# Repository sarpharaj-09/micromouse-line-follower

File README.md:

# Micromouse Line Follower

 **Project Status: In Development** 

A line-following micromouse robot project combining hardware design (KiCAD PCB layouts) with firmware development. This repository includes both Arduino Nano and ESP32 implementations, with comprehensive testing code and calibration tools.

## Overview

This project aims to build a reliable line-following robot using:
- **QTR-8 sensor array** for line detection
- **TB6612FNG motor driver** for motor control
- **Maze solving algorithm** with path simplification
- **PID control** for stable line following
- Dual MCU support: **ESP32** (primary) and **Arduino Nano** (testing)

The firmware includes motor control, PID tuning, sensor calibration, and a maze-solving algorithm that records and simplifies paths.

## Hardware

### Microcontrollers
- **ESP32 Development Board** (primary target)
- **Arduino Nano** (for testing and prototyping)

### Components
- **Motor Driver**: TB6612FNG
- **Line Sensors**: QTR-8 analog/RC sensor array
- **Motors**: DC motors for wheels
- **Power**: Battery pack
- **Display**: DM-OLED096 (0.96" OLED) - in design
- **Miscellaneous**: Jumper wires, resistors, capacitors

## Project Structure

```
micromouse-line-follower/
 Arduino_Nano/               # Arduino Nano PCB design (KiCAD)
    pcb_v1/                # Version 1 PCB layout
        DM-OLED096-636/    # OLED display footprint & symbol
        ESP32-DEVKIT-V1/   # ESP32 footprint & symbol
        MP1584_buck/       # Buck converter module
        kikad_dsign.*      # KiCAD project files
 ESP32/                      # ESP32 PCB design (KiCAD)
    pcb_v1/                # Version 1 PCB layout
        DM-OLED096-636/    # OLED display footprint & symbol
        ESP32-DEVKIT-V1/   # ESP32 footprint & symbol
        lineMazeSolver.*   # KiCAD project files
 micromouse_v1/             # Main firmware project (PlatformIO)
    micromouse_v1/
        platformio.ini     # PlatformIO configuration
        include/           # Header files
        lib/               # Dependencies (QTRSensors, TB6612FNG)
        src/
           main.cpp       # Main firmware with maze solving & PID
        test/              # Unit tests
 testing_phase_code/        # Standalone test sketches
    ESP32_test_code/       # ESP32-specific tests
       qtrSensor.ino     # QTR sensor test
    Nano_test_code/        # Arduino Nano tests
        Moter_test/        # Motor driver tests
        PID_Bluethooth/    # Bluetooth PID tuning
        plotter/           # Serial plotter data
        QTR_test/          # QTR sensor calibration
 README.md
```

## Firmware Features

### Current Implementation (main.cpp)
- **8-channel QTR sensor** integration with calibration
- **PID-based line following** with configurable gains (Kp, Kd)
- **Maze solving algorithm** with wall detection and path recording
- **Path simplification** to optimize shortest route
- **Motor control** with variable speed and direction
- **Turn decision logic** (left, straight, right)

### Pin Configuration (Arduino Nano)
```
Motor Control:
  - Motor 1: AIN1=4, AIN2=5, PWMA=3
  - Motor 2: BIN1=8, BIN2=9, PWMB=6
Control:
  - Switches: SW1=10, SW2=11, SW3=12
  - LED: 7
```

## Getting Started

### Prerequisites

- [PlatformIO](https://platformio.org/) (for ESP32 development)
- [Arduino IDE](https://www.arduino.cc/en/software) (for Nano sketches)
- Required libraries:
  - `SparkFun_TB6612` (Motor Driver)
  - `QTRSensors` (Line Sensor Array)

### Building & Uploading (PlatformIO/ESP32)

```powershell
cd micromouse_v1/micromouse_v1
pio run              # Build
pio run -t upload    # Upload to connected ESP32
```

### Testing (Arduino Nano)

1. Open Arduino IDE
2. Load a test sketch: `testing_phase_code/Nano_test_code/<test_folder>/<sketch>.ino`
3. Install dependencies via Library Manager
4. Select board (Arduino Nano) and COM port
5. Upload

### Test Sketches Available

| Sketch | Purpose |
|--------|---------|
| `Moter_test` | Test TB6612 motor driver (forward, backward, turn) |
| `QTR_test` | Read raw QTR sensor values and calibrate |
| `PID_Bluethooth` | Wireless PID tuning via Bluetooth serial |
| `plotter` | Stream sensor data for Serial Plotter visualization |

## Development Workflow

- **Feature branches**: Use `wip/*` prefix for work-in-progress branches
- **Main branch**: Keep stable with tested, documented commits
- **Testing**: Validate on both hardware and in simulation before merging
- **Documentation**: Update this README and code comments when adding features

## PCB Design Status

- **Arduino Nano v1**: In design phase - includes OLED display, buck converter
- **ESP32 v1**: In design phase - primary development board layout

## Troubleshooting

### Sensor Calibration Issues
- Run `QTR_test` to verify raw sensor values
- Check sensor array alignment over the line
- Verify power supply voltage (QTR operates 3.3-5V)

### Motor Control Issues
- Use `Moter_test` to verify TB6612 pin connections
- Check PWM pins are available on your MCU
- Verify motor power supply is adequate

### PID Tuning
- Use `PID_Bluethooth` for real-time parameter adjustment
- Start with low Kp/Kd values and increase gradually
- Monitor motor oscillation and response time

## Contributing

Contributions welcome! Please:
1. Create a feature branch (`wip/feature-name`)
2. Test thoroughly on hardware
3. Submit a pull request with clear description
4. Update documentation as needed

## License

This project is licensed under the terms specified in `LICENSE`.

---

**Last Updated**: January 2026  
**Note**: This project is actively developed. Features and documentation are updated frequently.

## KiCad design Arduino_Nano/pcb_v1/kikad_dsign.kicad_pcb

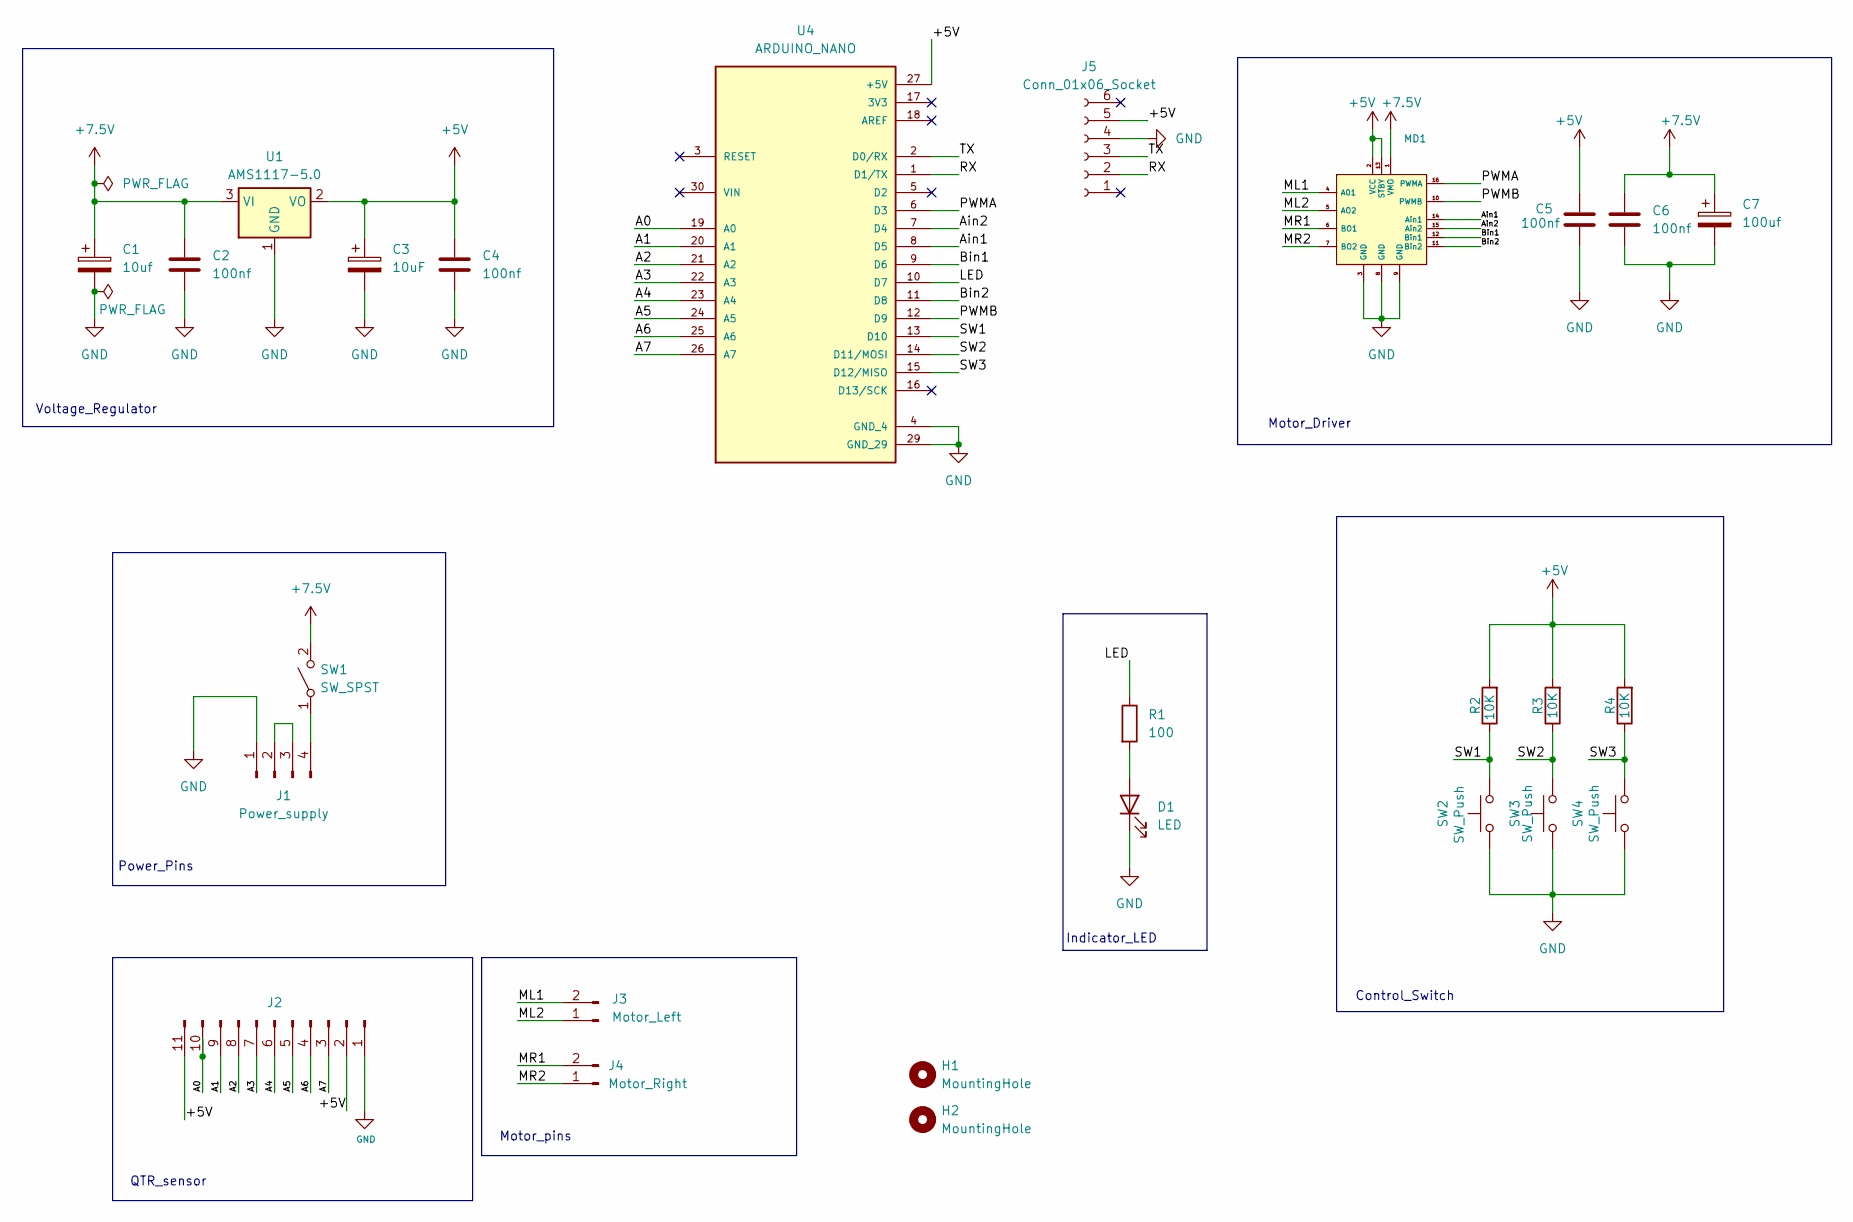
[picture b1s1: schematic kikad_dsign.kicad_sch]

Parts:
C1: 10uf; CP_Radial_D6.3mm_P2.50mm
C2, C4, C5, C6: 100nf; C_Disc_D3.8mm_W2.6mm_P2.50mm
C3: 10uF; CP_Radial_D6.3mm_P2.50mm
C7: 100uf; CP_Radial_D6.3mm_P2.50mm
D1: LED; LED_D5.0mm
H1, H2: MountingHole; MountingHole_2.5mm
J1: Power_supply; PinHeader_1x04_P2.54mm_Vertical
J2: Conn_01x11_Pin; PinHeader_1x11_P2.54mm_Vertical
J3: Motor_Left; PinHeader_1x02_P2.54mm_Vertical
J4: Motor_Right; PinHeader_1x02_P2.54mm_Vertical
J5: Conn_01x06_Socket
MD1: tbfng motor driver
R1: 100; R_Axial_DIN0207_L6.3mm_D2.5mm_P7.62mm_Horizontal
R2, R3, R4: 10K; R_Axial_DIN0207_L6.3mm_D2.5mm_P7.62mm_Horizontal
SW1: SW_SPST; PinHeader_1x02_P2.54mm_Vertical
SW2, SW3, SW4: SW_Push; SW_PUSH_6mm
U1: AMS1117-5.0; SOT-223-3_TabPin2
U4: ARDUINO_NANO; Arduino_Nano; PARTREV 30/06/2021

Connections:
+5V: C3.1, C4.1, C5.2, J2.2, J2.11, J5.5, MD1.2 (VCC), MD1.13 (STBY), R2.2, R3.2, R4.2, U1.2 (VO), U4.27 (+5V)
+7.5V: C1.1, C2.1, C6.1, C7.1, MD1.1 (VMO), SW1.2 (B), U1.3 (VI)
/A0: J2.10, U4.19 (A0)
/A1: J2.9, U4.20 (A1)
/A2: J2.8, U4.21 (A2)
/A3: J2.7, U4.22 (A3)
/A4: J2.6, U4.23 (A4)
/A5: J2.5, U4.24 (A5)
/A6: J2.4, U4.25 (A6)
/A7: J2.3, U4.26 (A7)
/Ain1: MD1.14 (Ain1), U4.8 (D5)
/Ain2: MD1.15 (Ain2), U4.7 (D4)
/Bin1: MD1.12 (Bin1), U4.9 (D6)
/Bin2: MD1.11 (Bin2), U4.11 (D8)
/LED: R1.1, U4.10 (D7)
/ML1: J3.2, MD1.4 (A01)
/ML2: J3.1, MD1.5 (AO2)
/MR1: J4.2, MD1.6 (BO1)
/MR2: J4.1, MD1.7 (BO2)
/PWMA: MD1.16 (PWMA), U4.6 (D3)
/PWMB: MD1.10 (PWMB), U4.12 (D9)
/RX: J5.2, U4.1 (D1/TX)
/SW1: R2.1, SW2.2, U4.13 (D10)
/SW2: R3.1, SW3.2, U4.14 (D11/MOSI)
/SW3: R4.1, SW4.2, U4.15 (D12/MISO)
/TX: J5.3, U4.2 (D0/RX)
GND: C1.2, C2.2, C3.2, C4.2, C5.1, C6.2, C7.2, D1.1 (K), J1.1, J2.1, J5.4, MD1.3 (GND), MD1.8 (GND), MD1.9 (GND), SW2.1, SW3.1, SW4.1, U1.1 (GND), U4.4 (GND_4), U4.29 (GND_29)
unnamed: D1.2 (A), R1.2
unnamed: J1.2, J1.3
unnamed: J1.4, SW1.1 (A)

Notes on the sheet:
Motor_Driver
QTR_sensor
Power_Pins
Motor_pins
Voltage_Regulator
Indicator_LED
Control_Switch

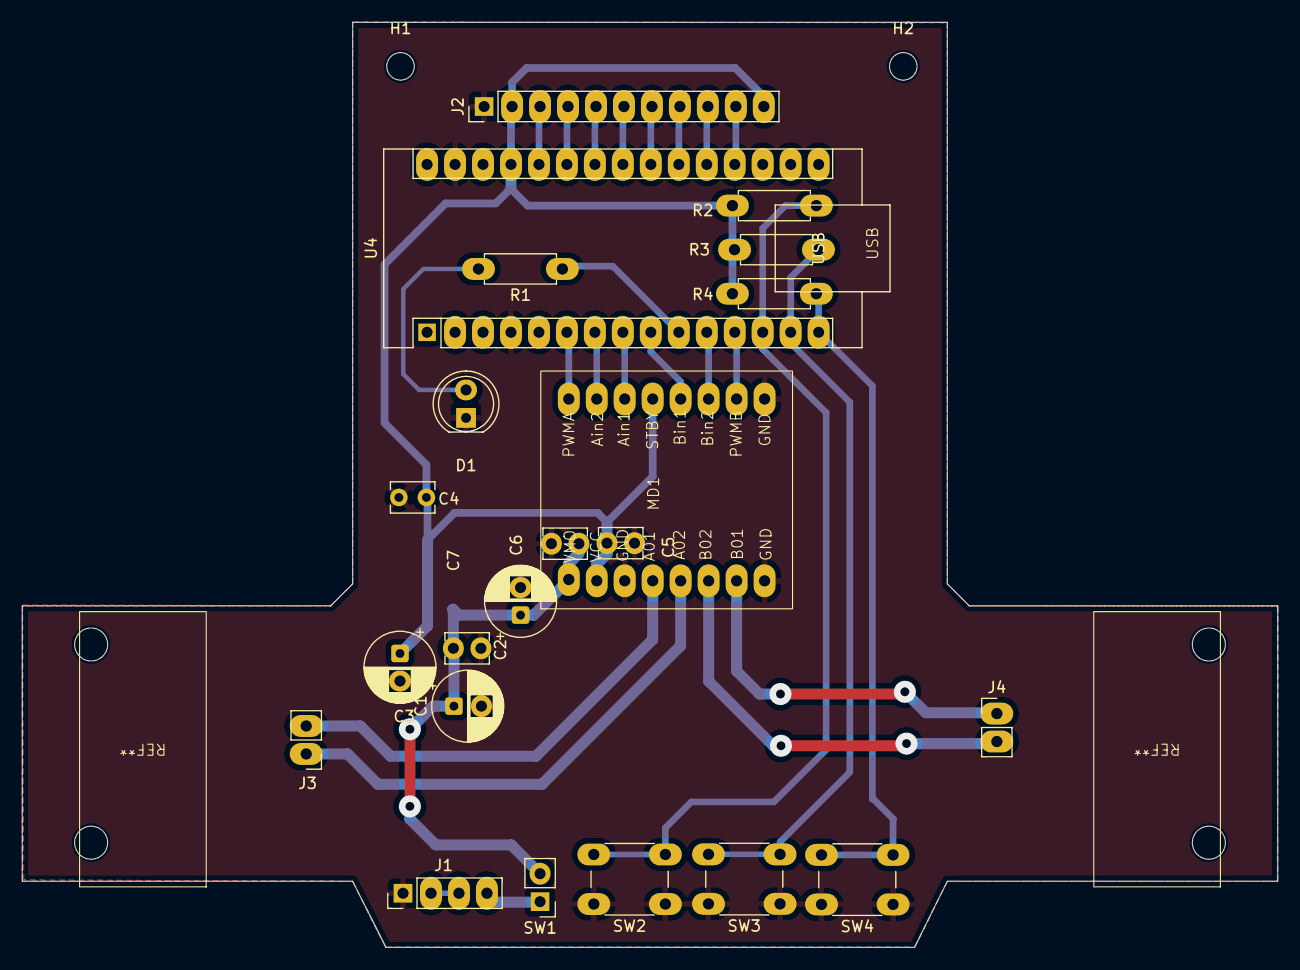
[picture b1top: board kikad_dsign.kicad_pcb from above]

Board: 2 copper layers, 114.0 x 84.0 mm, 25 parts (1 on the bottom side), 28 nets.

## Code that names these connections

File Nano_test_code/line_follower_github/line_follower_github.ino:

// Download below two library on your arduino IDE you will get this from google
#include <SparkFun_TB6612.h>  // This libaray is for sparkfun motor driver  
#include <QTRSensors.h>       // It is for qtr sensors 

// Initialization of the motors
#define AIN1 8
#define BIN1 5
#define AIN2 9
#define BIN2 4
#define PWMA 6
#define PWMB 3
#define STBY 10

const int offsetA = 1;
const int offsetB = 1;

// Initialization of the controls
#define sw1 10    // START switch
#define sw2 11    // CALIBRATE switch
#define led 7
int s1;
int s2;

// Initialization of sensors
#define NUM_SENSORS 8
unsigned int sensors1[8];
int thr[8];

// Initialization of PID parameter
#define MaxSpeed 250
#define BaseSpeed 250
int lastError = 0;
float kp = 0.1;
float kd = 0.3;
int last_pos = 3500;

// Creating the instance of class for motor and sensors
Motor motor1 = Motor(AIN1, AIN2, PWMA, offsetA, STBY);
Motor motor2 = Motor(BIN1, BIN2, PWMB, offsetB, STBY);
QTRSensors qtra;

void setup()
{
  qtra.setTypeAnalog();
  qtra.setSensorPins((const uint8_t[]) {
    A0, A1, A2, A3, A4, A5, A6, A7
  }, NUM_SENSORS);

  pinMode(sw1, INPUT_PULLUP);
  pinMode(sw2, INPUT_PULLUP);
  pinMode(led, OUTPUT);
  pinMode(13, OUTPUT);

  digitalWrite(STBY, HIGH);
  digitalWrite(13, LOW);

  Serial.begin(9600);

  // ---------- WAIT FOR SW2 TO CALIBRATE ----------
  Serial.println("Press SW2 to CALIBRATE.");
  while (digitalRead(sw2) == HIGH);  // Wait for press  
  calibration();                     // Run calibration
  delay(500);
  Serial.println("Calibration complete.");
}

void loop() {

  // ---------- WAIT FOR SW1 TO START ----------
  Serial.println("Press SW1 to START following line.");
  while (digitalRead(sw1) == HIGH);  // Wait for press

  // Soft Start
  forward(motor1, motor2, 60);  delay(40);
  forward(motor1, motor2, 80);  delay(40);
  forward(motor1, motor2, 100); delay(40);

  follow_segment1();
}



// ---------------------------------------------------------------
//                    CALIBRATION FUNCTION
// ---------------------------------------------------------------
void calibration()
{
  for (int i = 0; i <= 100; i++)
  {
    if (i < 25 || i >= 75)
      left(motor1, motor2, 255);
    else
      right(motor1, motor2, 255);

    qtra.calibrate();
    delay(10);
  }

  brake(motor1, motor2);

  Serial.println("Minimum values:");
  for (int i = 0; i < NUM_SENSORS; i++) {
    Serial.print(qtra.calibrationOn.minimum[i]);
    Serial.print(' ');
    thr[i] = (qtra.calibrationOn.minimum[i] + qtra.calibrationOn.maximum[i]) / 2;
  }

  Serial.println("\nMaximum values:");
  for (int i = 0; i < NUM_SENSORS; i++) {
    Serial.print(qtra.calibrationOn.maximum[i]);
    Serial.print(' ');
  }

  Serial.println("\nThresholds:");
  Serial.println(thr[0]);
  Serial.println(thr[7]);
}



// ---------------------------------------------------------------
//                 LINE FOLLOWING FUNCTION
// ---------------------------------------------------------------
void follow_segment1()
{
  while (1) {   // Keep following line

    int position = qtra.readLineWhite(sensors1);
    int error = 3500 - position;

    int motorSpeed = kp * error + kd * (error - lastError);
    lastError = error;

    int rightMotorSpeed = BaseSpeed - motorSpeed;
    int leftMotorSpeed  = BaseSpeed + motorSpeed;

    if (rightMotorSpeed > MaxSpeed ) rightMotorSpeed = MaxSpeed;
    if (leftMotorSpeed  > MaxSpeed ) leftMotorSpeed  = MaxSpeed;
    if (rightMotorSpeed < 0) rightMotorSpeed = 0;
    if (leftMotorSpeed  < 0) leftMotorSpeed  = 0;

    motor1.drive(rightMotorSpeed);
    motor2.drive(leftMotorSpeed);

    delay(1);
  }
}

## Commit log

2025-09-27 feat: ESP32 line follower with PID control and multi-sensor support
2025-11-13 Datasheet ESP32
2025-11-19 Added component datasheet in separate folder
2025-11-19 Uploaded correct motor driver datasheet
2025-11-19 Updated Readme file.
2025-11-25 Added linefollower code with wireless PID tuning
2025-11-25 Organized project structure
2025-11-25 Modified README file.
2025-11-27 Added plotter for PID variable
2025-12-03 Added ESP32 based PCB Design
2025-12-03 Organized code
2025-12-04 Added Line Maze Solver Code for Arduino NANO
2025-12-04 Edited Design
2025-12-10 Resolved maze solving logic
2025-12-10 Added PCB Design for Arduino nano
2025-12-10 Added a new features with NANO Based pcb PCB
2026-01-16 Renamed and Rearranged files.
